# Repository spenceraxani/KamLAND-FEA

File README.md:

# KamLAND-FEA
The analog front end for MOGURA2

Datasheets:
 	This folder contains the datasheets for the desired op amps, the RF-SoC prototype board (ZCU111) and the expansion board (XM5000).

Documents:
	This contains the detailed description of the front end analog electronics reference design.

KiCAD:
	Here, the PCB design files are included for the RF-ADC and RF-DAC expansion boards.

Simulation:
	Files for the TINA-TI simulation.

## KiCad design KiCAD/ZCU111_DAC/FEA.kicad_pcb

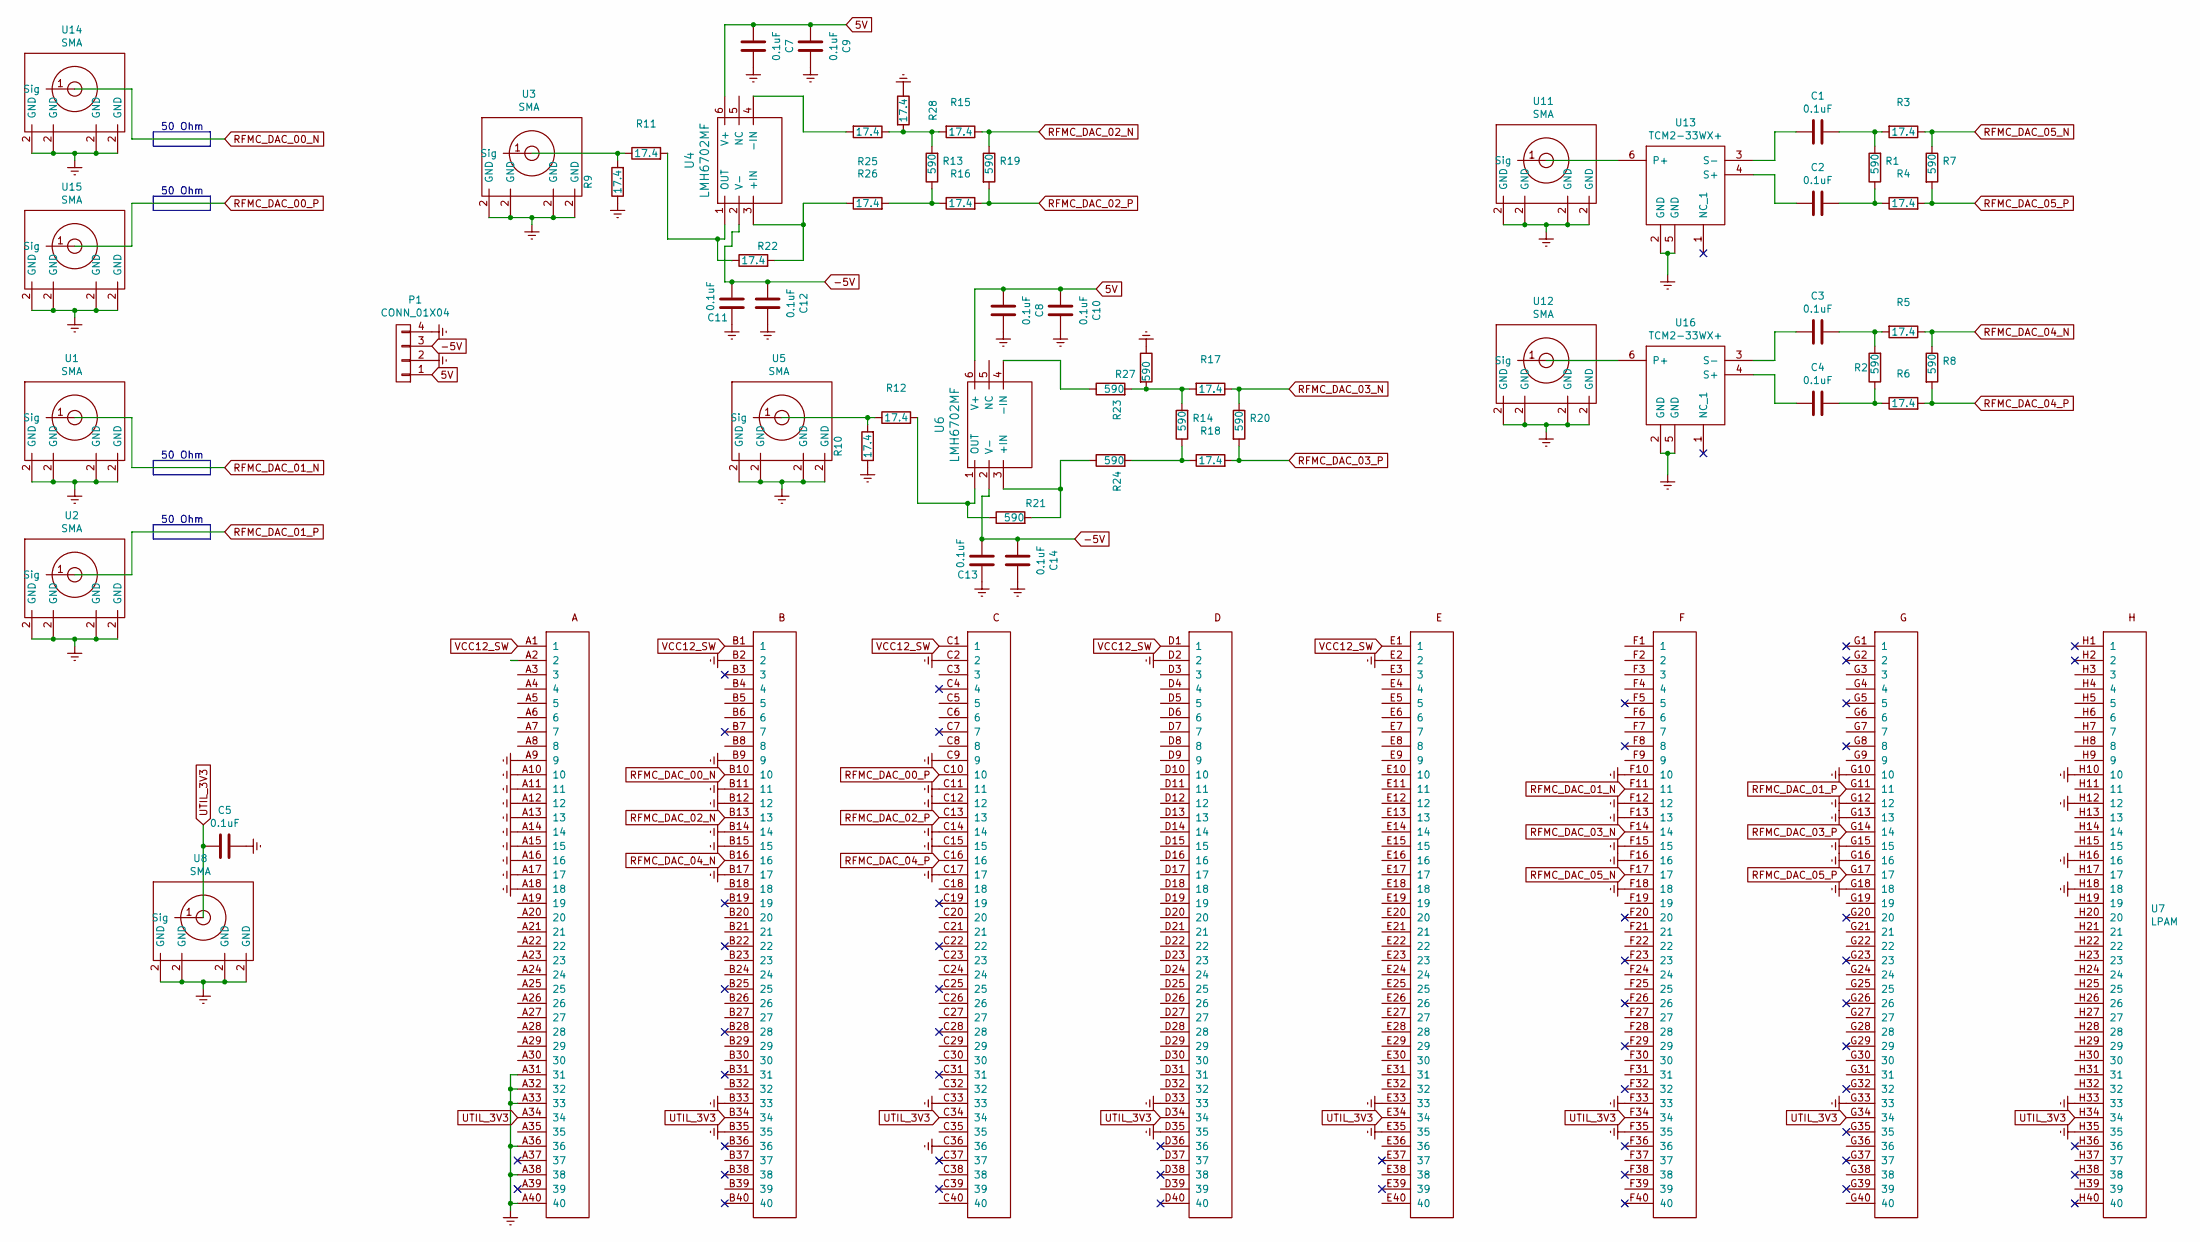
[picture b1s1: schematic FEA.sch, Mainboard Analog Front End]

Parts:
C1, C2, C3, C4, C5, C7, C8, C9, C10, C11, C12, C13, C14: 0.1uF; C_0603
P1: CONN_01X04; Pin_Header_Straight_1x04_Pitch2.54mm
R1, R2, R7, R8, R13, R14, R19, R20, R21, R23, R24, R27: 590; C_0603
R3, R4, R5, R6, R9, R10, R11, R12, R15, R16, R17, R18, R22, R25, R26, R28: 17.4; C_0603
U1, U2, U3, U5, U11, U12, U14, U15: SMA; SMA_90
U4, U6: LMH6702MF; SOT-23-6
U7: LPAM
U8: SMA; SMA_side_mount
U13, U16: TCM2-33WX+

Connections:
5V: C7.2, C8.2, C9.2, C10.2, P1.1, U4.6 (V+), U6.6 (V+)
-5V: C11.2, C12.2, C13.2, C14.2, P1.3, U4.2 (V-), U6.2 (V-)
Earth: C5.1, C7.1, C8.1, C9.1, C10.1, C11.1, C12.1, C13.1, C14.1, P1.2, P1.4, R9.1, R10.1, R27.1, R28.1, U1.2 (GND), U2.2 (GND), U3.2 (GND), U5.2 (GND), U7.A9 (9), U7.A10 (10), U7.A11 (11), U7.A12 (12), U7.A13 (13), U7.A14 (14), U7.A15 (15), U7.A16 (16), U7.A17 (17), U7.A18 (18), U7.A31 (31), U7.A32 (32), U7.A33 (33), U7.A36 (36), U7.A38 (38), U7.A40 (40), U7.B2 (2), U7.B9 (9), U7.B11 (11), U7.B12 (12), U7.B14 (14), U7.B15 (15), U7.B17 (17), U7.B33 (33), U7.B35 (35), U7.C2 (2), U7.C9 (9), U7.C11 (11), U7.C12 (12), U7.C14 (14), U7.C15 (15), U7.C17 (17), U7.C33 (33), U7.C36 (36), U7.D2 (2), U7.D33 (33), U7.D35 (35), U7.E2 (2), U7.E33 (33), U7.E35 (35), U7.F10 (10), U7.F12 (12), U7.F13 (13), U7.F15 (15), U7.F16 (16), U7.F18 (18), U7.F33 (33), U7.F35 (35), U7.G10 (10), U7.G12 (12), U7.G13 (13), U7.G15 (15), U7.G16 (16), U7.G18 (18), U7.G33 (33), U7.H10 (10), U7.H12 (12), U7.H16 (16), U7.H18 (18), U7.H33 (33), U7.H35 (35), U8.2 (GND), U11.2 (GND), U12.2 (GND), U13.2 (GND), U13.5 (GND), U14.2 (GND), U15.2 (GND), U16.2 (GND), U16.5 (GND)
unnamed: C1.1, R1.2, R3.2
unnamed: C1.2, U13.3 (S-)
unnamed: C2.1, R1.1, R4.1
unnamed: C2.2, U13.4 (S+)
unnamed: C3.1, R2.2, R5.2
unnamed: C3.2, U16.3 (S-)
unnamed: C4.1, R2.1, R6.1
unnamed: C4.2, U16.4 (S+)
unnamed: R10.2, R12.1, U5.1 (Sig)
unnamed: R9.2, R11.1, U3.1 (Sig)
unnamed: R11.2, R22.1, U4.1 (OUT)
unnamed: R12.2, R21.1, U6.1 (OUT)
unnamed: R13.1, R16.1, R26.2
unnamed: R13.2, R15.2, R25.1, R28.2
unnamed: R14.1, R18.1, R24.2
unnamed: R14.2, R17.2, R23.2, R27.2
unnamed: R21.2, R24.1, U6.3 (+IN)
unnamed: R22.2, R26.1, U4.3 (+IN)
unnamed: R23.1, U6.4 (-IN)
unnamed: R25.2, U4.4 (-IN)
unnamed: U11.1 (Sig), U13.6 (P+)
unnamed: U12.1 (Sig), U16.6 (P+)
RFMC_DAC_00_N: U7.B10 (10), U14.1 (Sig)
RFMC_DAC_00_P: U7.C10 (10), U15.1 (Sig)
RFMC_DAC_01_N: U1.1 (Sig), U7.F11 (11)
RFMC_DAC_01_P: U2.1 (Sig), U7.G11 (11)
RFMC_DAC_02_N: R15.1, R19.1, U7.B13 (13)
RFMC_DAC_02_P: R16.2, R19.2, U7.C13 (13)
RFMC_DAC_03_N: R17.1, R20.1, U7.F14 (14)
RFMC_DAC_03_P: R18.2, R20.2, U7.G14 (14)
RFMC_DAC_04_N: R5.1, R8.1, U7.B16 (16)
RFMC_DAC_04_P: R6.2, R8.2, U7.C16 (16)
RFMC_DAC_05_N: R3.1, R7.1, U7.F17 (17)
RFMC_DAC_05_P: R4.2, R7.2, U7.G17 (17)
UTIL_3V3: C5.2, U7.A34 (34), U7.B34 (34), U7.C34 (34), U7.D34 (34), U7.E34 (34), U7.F34 (34), U7.G34 (34), U7.H34 (34), U8.1 (Sig)
VCC12_SW: U7.A1 (1), U7.B1 (1), U7.C1 (1), U7.D1 (1), U7.E1 (1)

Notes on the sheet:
50 Ohm

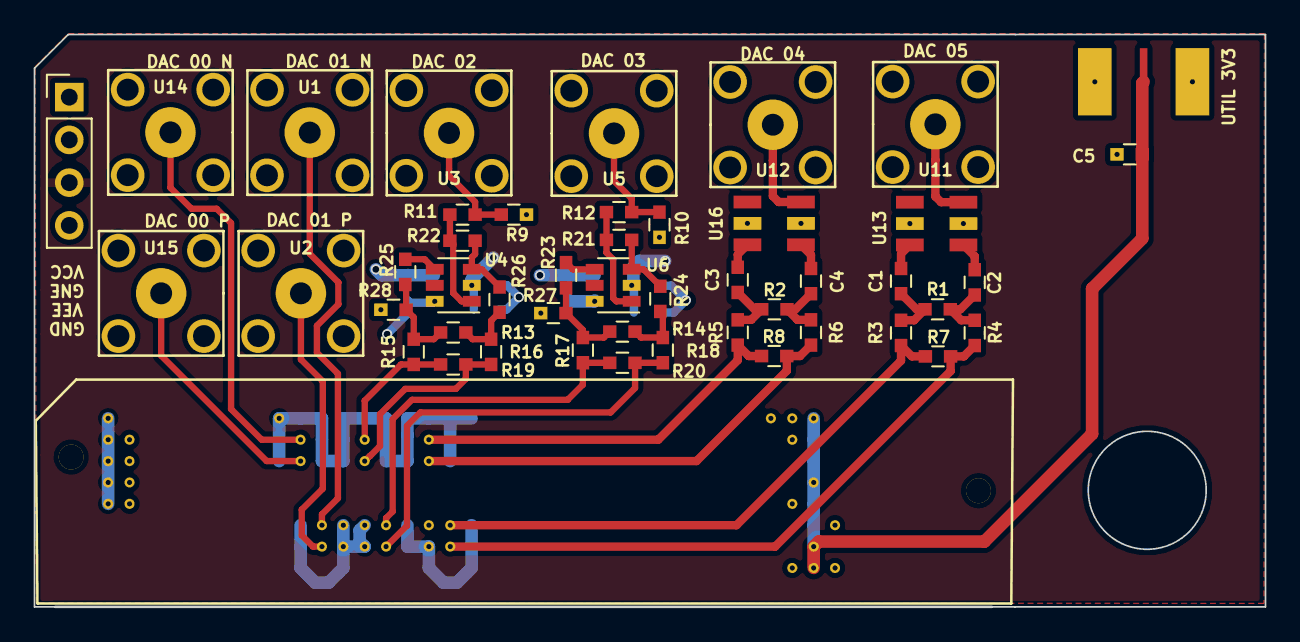
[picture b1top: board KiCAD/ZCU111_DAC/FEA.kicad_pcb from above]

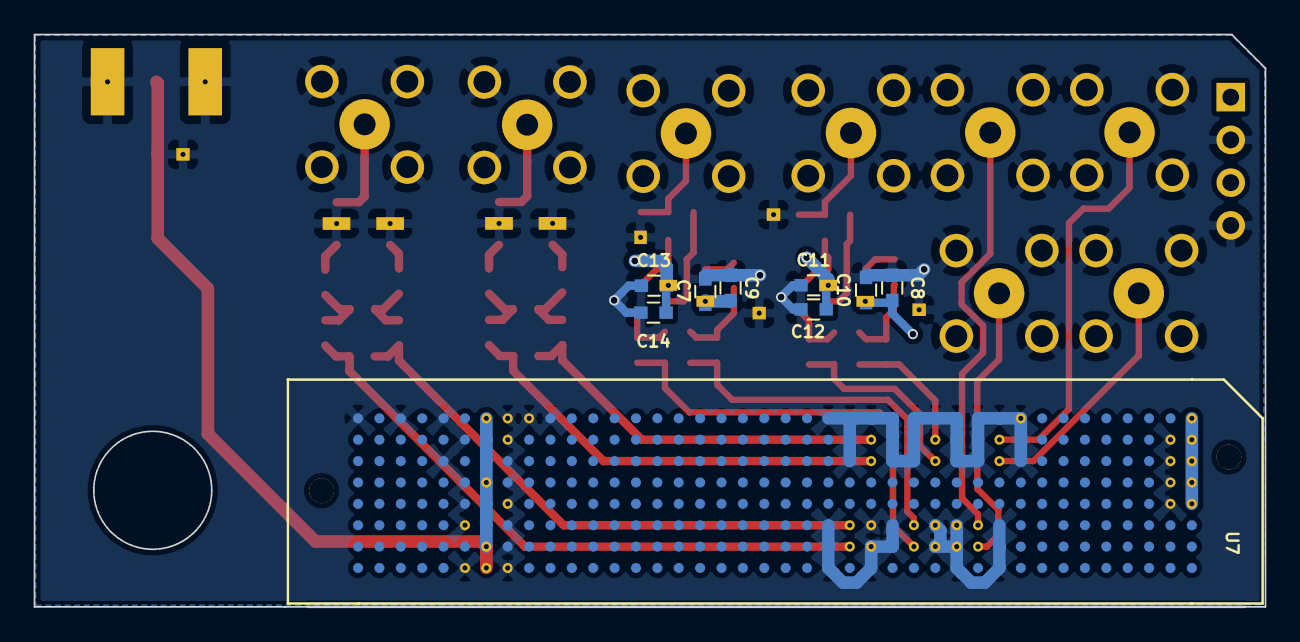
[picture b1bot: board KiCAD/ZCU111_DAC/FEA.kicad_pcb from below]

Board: 4 copper layers, 73.1 x 34.0 mm, 56 parts (9 on the bottom side), 39 nets.

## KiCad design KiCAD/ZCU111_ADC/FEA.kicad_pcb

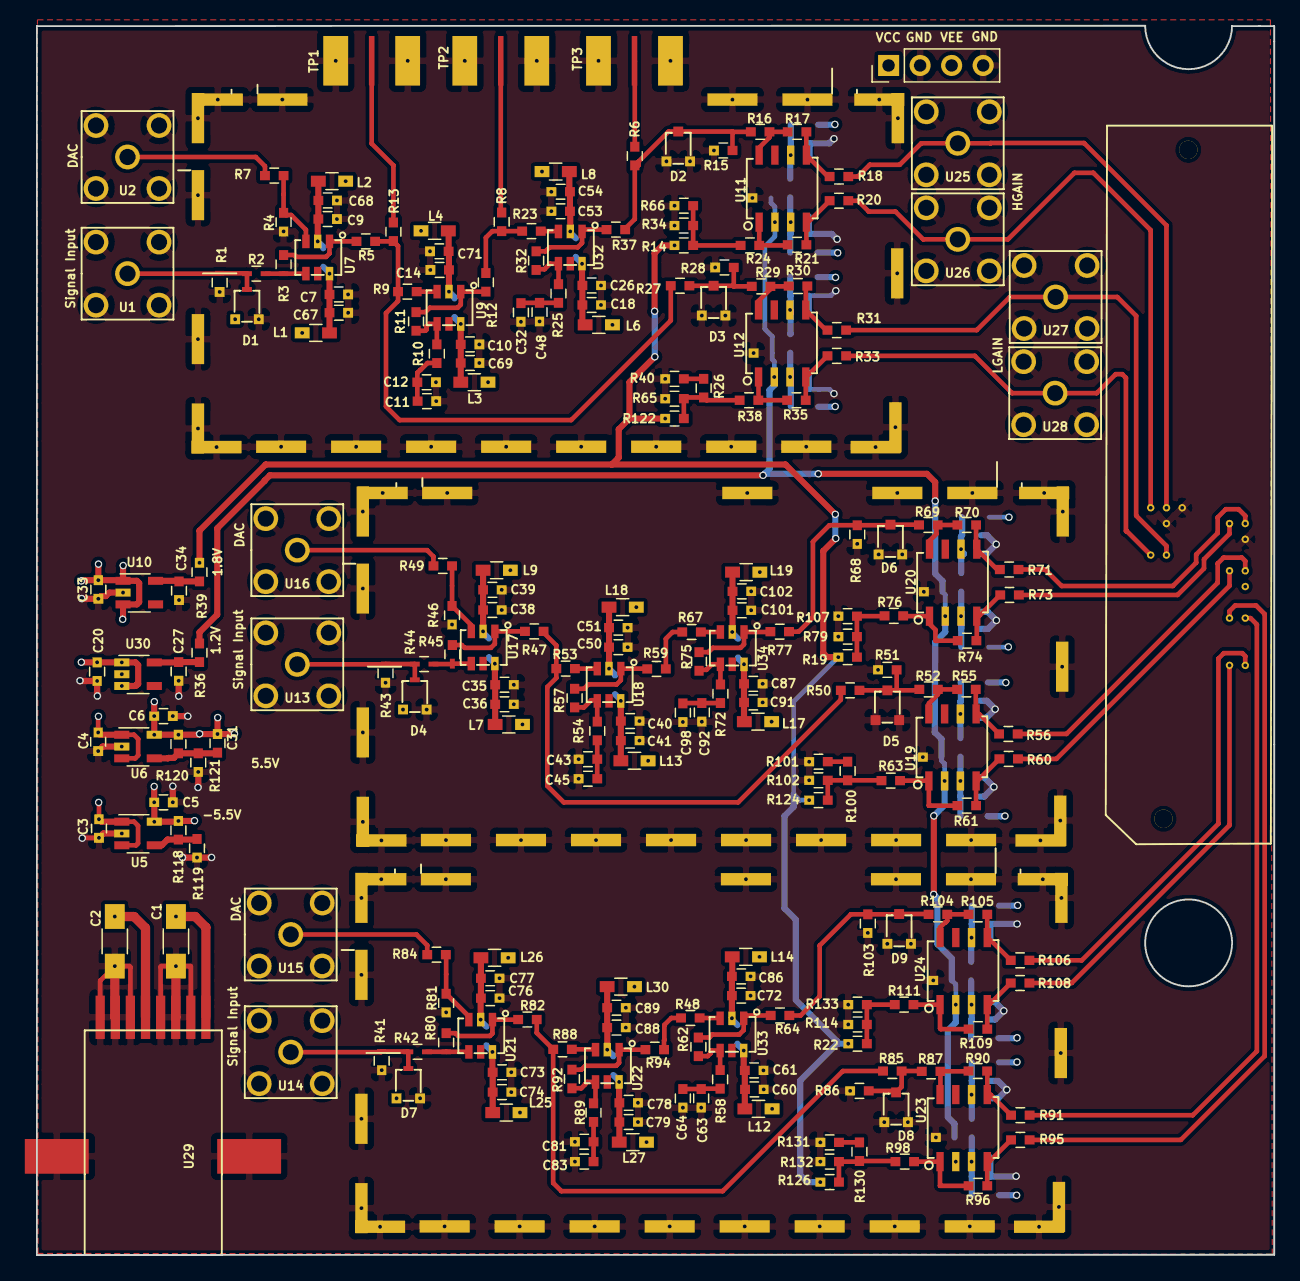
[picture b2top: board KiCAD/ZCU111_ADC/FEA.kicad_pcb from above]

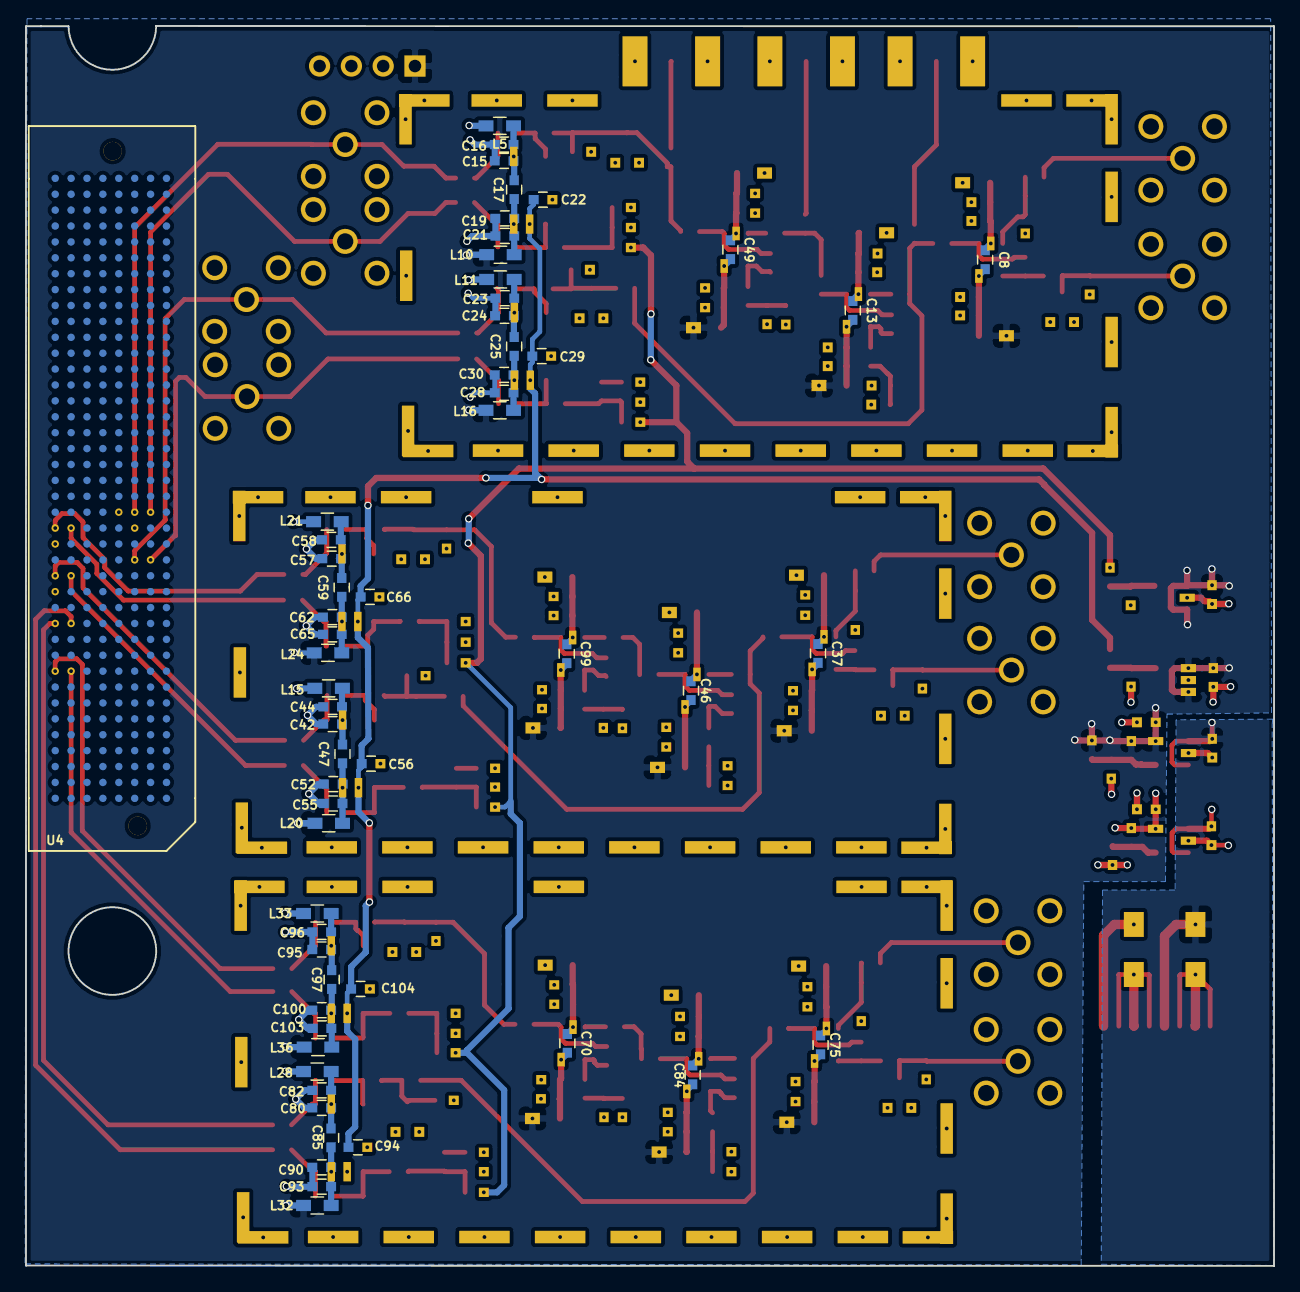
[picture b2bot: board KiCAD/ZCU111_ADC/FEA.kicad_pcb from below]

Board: 4 copper layers, 99.7 x 99.1 mm, 298 parts (58 on the bottom side), 142 nets.

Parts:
C1, C2: CP1; C_1206_HandSoldering
C3, C5, C6: 2.2uF; C_0603
C4, C20, C33: 1uF; C_0603
C7, C8, C9, C10, C11, C13, C14, C16, C19, C24, C26, C30, C32, C36, C37, C38, C41, C43, C44, C46, C49, C50, C52, C53, C58, C61, C62, C63, C70, C72, C74, C75, C76, C79, C81, C82, C84, C88, C90, C91, C92, C96, C99, C100, C101: 10nF; C_0603
C12, C45, C48, C64, C83, C98: 100nF; C_0603
C15, C18, C21, C22, C23, C28, C29, C35, C40, C42, C51, C54, C55, C56, C57, C60, C65, C66, C67, C69, C71, C73, C78, C80, C86, C87, C89, C93, C94, C95, C102, C103, C104: 0.1uF; C_0603
C17, C25, C47, C59, C85, C97: 0.01uF; C_0603
C27, C34: 10uF; C_0603
C31: 470pF; C_0603
C39, C68, C77: 0.1nF; C_0603
D1, D2, D3, D4, D5, D6, D7, D8, D9: RB706D
L1, L2, L3, L4, L5, L6, L7, L8, L9, L10, L11, L12, L13, L14, L15, L16, L17, L18, L19, L20, L21, L24, L25, L26, L27, L28, L30, L32, L33, L36: BLM18BB221SN1; R_0603_HandSoldering
P1: CONN_01X04; Pin_Header_Straight_1x04_Pitch2.54mm
P2, P3, P4: CONN_01X01; RF SHIELD 1.094 X 2.23 SMD
R1, R41, R43: 54.9; C_0603
R2, R3, R42, R44, R45, R80: 560; C_0603
R4, R46, R81: 25.5; C_0603
R5, R9, R12, R18, R20, R23, R26, R28, R31, R33, R37, R47, R48, R51, R53, R56, R59, R60, R64, R65, R66, R67, R71, R73, R77, R82, R86, R88, R91, R94, R95, R100, R102, R106, R107, R108, R130, R132, R133: 49.9; C_0603
R6, R8, R13: R; C_0603
R7, R49, R84: 10k; C_0603
R10, R25, R54, R58, R72, R89: 100; C_0603
R11, R32, R57, R62, R75, R92: 390; C_0603
R14, R19, R22, R27, R40, R50, R85, R101, R122, R124, R126, R131: 200; C_0603
R15, R34, R68, R79, R103, R114: 68.1; C_0603
R16, R24, R69, R76, R104, R111: 127; C_0603
R17, R21, R30, R35, R55, R61, R70, R74, R90, R96, R105, R109: 274; C_0603
R29, R38, R52, R63, R87, R98: 255; C_0603
R36, R39: 0; C_0603
R118: 21k; C_0603
R119, R121: 75k; C_0603
R120: 22.1k; C_0603
U1, U2, U13, U14, U15, U16, U25, U26, U27, U28: SMA; SMA_90
U3, U8, U31: SMA; SMA_side_mount
U4: LPAM
U5, U6, U10, U30: 5-Lead_TSOT; TSOT-23-5
U7, U9, U17, U18, U21, U22, U32, U33, U34: LMH6702MF; LMH6702
U11, U12, U19, U20, U23, U24: LMH6550
U29: Ethernet

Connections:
1.2V: C22.1, C29.1, C56.1, C66.1, C94.1, C104.1, R36.1, U4.A21, U11.2, U12.2, U19.2, U20.2, U23.2, U24.2
1.8V: R14.2, R19.2, R22.2, R39.1, R122.2, R124.2, R126.2
5V: C6.1, C20.1, C31.2, C33.1, L1.2, L3.2, L6.2, L7.2, L10.1, L12.2, L13.2, L16.1, L17.2, L20.1, L24.1, L25.2, L27.2, L32.1, L36.1, P1.1, R120.2, U6.5, U10.1, U10.3, U30.1, U30.3
-5V: C5.1, D1.2, D4.2, D7.2, L2.1, L4.1, L5.2, L8.1, L9.1, L11.2, L14.1, L15.2, L18.1, L19.1, L21.2, L26.1, L28.2, L30.1, L33.2, P1.3, R118.1, U5.5
/Amp1/DAC_input: R7.1, U2.1
/Amp1/Sig_in: D1.3, R1.1, R2.2, U1.1
/Amp1/TP1: R5.1, R9.2, R13.1, R27.2
/Amp1/TP2: R8.1, R12.1, R23.2
/Amp1/TP3: D2.3, R6.1, R15.1, R16.2, R37.1
/sheet5EE0D7D6/DAC_input: R49.1, U16.1
/sheet5EE0D7D6/Sig_in: D4.3, R43.1, R44.2, U13.1
/sheet5EE0D7D6/TP1: R47.1, R50.2, R53.2
/sheet5EE0D7D6/TP2: R59.1, R67.2
/sheet5EE0D7D6/TP3: D6.3, R68.1, R69.2, R77.1
/sheet5F00471B/DAC_input: R84.1, U15.1
/sheet5F00471B/Sig_in: D7.3, R41.1, R42.2, U14.1
/sheet5F00471B/TP1: R82.1, R85.2, R88.2
/sheet5F00471B/TP2: R48.2, R94.1
/sheet5F00471B/TP3: D9.3, R64.1, R103.1, R104.2
Earth: C1.2, C2.1, C3.2, C4.2, C5.2, C6.2, C7.1, C9.1, C10.1, C11.1, C12.1, C14.1, C15.1, C16.1, C18.1, C19.1, C20.2, C21.1, C22.2, C23.1, C24.1, C26.1, C27.2, C28.1, C29.2, C30.1, C32.1, C33.2, C34.2, C35.1, C36.1, C38.1, C39.1, C40.1, C41.1, C42.1, C43.1, C44.1, C45.1, C48.1, C50.1, C51.1, C52.1, C53.1, C54.1, C55.1, C56.2, C57.1, C58.1, C60.1, C61.1, C62.1, C63.1, C64.1, C65.1, C66.2, C67.1, C68.1, C69.1, C71.1, C72.1, C73.1, C74.1, C76.1, C77.1, C78.1, C79.1, C80.1, C81.1, C82.1, C83.1, C86.1, C87.1, C88.1, C89.1, C90.1, C91.1, C92.1, C93.1, C94.2, C95.1, C96.1, C98.1, C100.1, C101.1, C102.1, C103.1, C104.2, D1.1, D2.1, D2.2, D3.1, D3.2, D4.1, D5.1, D5.2, D6.1, D6.2, D7.1, D8.1, D8.2, D9.1, D9.2, P1.2, P1.4, P2.1, P3.1, P4.1, R1.2, R4.1, R15.2, R28.2, R34.1, R40.1, R41.2, R43.2, R46.1, R51.2, R65.1, R66.1, R68.2, R79.1, R81.1, R86.2, R101.1, R102.1, R103.2, R107.1, R114.1, R119.1, R121.1, R131.1, R132.1, R133.1, U1.2, U2.2, U3.2, U4.A5, U4.A8, U4.B15, U4.C15, U4.C18, U4.D19, U4.H17, U5.2, U6.2, U8.2, U10.2, U13.2, U14.2, U15.2, U16.2, U25.2, U26.2, U27.2, U28.2, U29.0, U29.1, U29.2, U29.3, U29.5, U29.6, U29.7, U30.2, U31.2
unnamed: C1.1, C3.1, U5.1, U5.3, U29.8
unnamed: C2.2, C4.1, U6.1, U6.3, U29.4
unnamed: C10.2, C13.2, C69.2, L3.1, U9.6
unnamed: C11.2, C12.2, R10.1
unnamed: C13.1, C14.2, C71.2, L4.2, U9.2
unnamed: C15.2, C16.2, C17.2, L5.1, U11.6
unnamed: C17.1, C19.2, C21.2, L10.2, U11.3
unnamed: C18.2, C26.2, C49.2, L6.1, U32.6
unnamed: C23.2, C24.2, C25.2, L11.1, U12.6
unnamed: C25.1, C28.2, C30.2, L16.2, U12.3
unnamed: C27.1, R36.2, U30.5
unnamed: C31.1, R120.1, R121.2, U6.4
unnamed: C32.2, C48.2, R25.1
unnamed: C34.1, R39.2, U10.5
unnamed: C35.2, C36.2, C37.2, L7.1, U17.6
unnamed: C37.1, C38.2, C39.2, L9.2, U17.2
unnamed: C40.2, C41.2, C46.2, L13.1, U18.6
unnamed: C42.2, C44.2, C47.2, L15.1, U19.6
unnamed: C43.2, C45.2, R54.1
unnamed: C46.1, C50.2, C51.2, L18.2, U18.2
unnamed: C47.1, C52.2, C55.2, L20.2, U19.3
unnamed: C49.1, C53.2, C54.2, L8.2, U32.2
unnamed: C57.2, C58.2, C59.2, L21.1, U20.6
unnamed: C59.1, C62.2, C65.2, L24.2, U20.3
unnamed: C60.2, C61.2, C70.2, L12.1, U33.6
unnamed: C63.2, C64.2, R58.1
unnamed: C7.2, C8.2, C67.2, L1.1, U7.6
unnamed: C8.1, C9.2, C68.2, L2.2, U7.2
unnamed: C70.1, C72.2, C86.2, L14.2, U33.2
unnamed: C73.2, C74.2, C75.2, L25.1, U21.6
unnamed: C75.1, C76.2, C77.2, L26.2, U21.2
unnamed: C78.2, C79.2, C84.2, L27.1, U22.6
unnamed: C80.2, C82.2, C85.2, L28.1, U23.6
unnamed: C81.2, C83.2, R89.1
unnamed: C84.1, C88.2, C89.2, L30.2, U22.2
unnamed: C85.1, C90.2, C93.2, L32.2, U23.3
unnamed: C87.2, C91.2, C99.2, L17.1, U34.6
unnamed: C92.2, C98.2, R72.1
unnamed: C95.2, C96.2, C97.2, L33.1, U24.6
unnamed: C97.1, C100.2, C103.2, L36.2, U24.3
unnamed: C99.1, C101.2, C102.2, L19.2, U34.2
unnamed: D3.3, R27.1, R28.1, R29.2
unnamed: D5.3, R50.1, R51.1, R52.2
unnamed: D8.3, R85.1, R86.1, R87.2
unnamed: R2.1, R3.2, U7.4
unnamed: R3.1, R5.2, U7.1
unnamed: R4.2, R7.2, U7.3
unnamed: R6.2, U31.1
unnamed: R8.2, U3.1
unnamed: R9.1, U9.3
unnamed: R10.2, R11.2, U9.4
unnamed: R11.1, R12.2, U9.1
unnamed: R13.2, U8.1
unnamed: R14.1, R24.2, R34.2, R66.2
unnamed: R16.1, R17.2, U11.8
unnamed: R17.1, R18.2, U11.5
unnamed: R20.2, R21.2, U11.4
unnamed: R21.1, R24.1, U11.1
unnamed: R23.1, U32.3
unnamed: R25.2, R32.2, U32.4
unnamed: R26.1, R40.2
unnamed: R29.1, R30.2, U12.8
unnamed: R30.1, R31.2, U12.5
unnamed: R32.1, R37.2, U32.1
unnamed: R33.2, R35.2, U12.4
unnamed: R35.1, R38.1, U12.1
unnamed: R42.1, R80.2, U21.4
unnamed: R44.1, R45.2, U17.4
unnamed: R45.1, R47.2, U17.1
unnamed: R46.2, R49.2, U17.3
unnamed: R48.1, U33.3
unnamed: R52.1, R55.2, U19.8
unnamed: R53.1, U18.3
unnamed: R54.2, R57.2, U18.4
unnamed: R55.1, R56.2, U19.5
unnamed: R57.1, R59.2, U18.1
unnamed: R58.2, R62.2, U33.4
unnamed: R60.2, R61.2, U19.4
unnamed: R61.1, R63.1, U19.1
unnamed: R62.1, R64.2, U33.1
unnamed: R67.1, U34.3
unnamed: R69.1, R70.2, U20.8
unnamed: R70.1, R71.2, U20.5
unnamed: R72.2, R75.2, U34.4
unnamed: R73.2, R74.2, U20.4
unnamed: R74.1, R76.1, U20.1
unnamed: R75.1, R77.2, U34.1
unnamed: R80.1, R82.2, U21.1
unnamed: R81.2, R84.2, U21.3
unnamed: R87.1, R90.2, U23.8
unnamed: R88.1, U22.3
unnamed: R89.2, R92.2, U22.4
unnamed: R90.1, R91.2, U23.5
unnamed: R92.1, R94.2, U22.1
unnamed: R95.2, R96.2, U23.4
unnamed: R96.1, R98.1, U23.1
unnamed: R100.1, R101.2
unnamed: R63.2, R100.2, R102.2, R124.1
unnamed: R104.1, R105.2, U24.8
unnamed: R105.1, R106.2, U24.5
unnamed: R19.1, R76.2, R79.2, R107.2
unnamed: R108.2, R109.2, U24.4
unnamed: R109.1, R111.1, U24.1
unnamed: R22.1, R111.2, R114.2, R133.2
unnamed: R118.2, R119.2, U5.4
unnamed: R26.2, R38.2, R65.2, R122.1
unnamed: R98.2, R126.1, R130.2, R132.2
unnamed: R130.1, R131.2
RFMC_ADC_00_N: R108.1, U4.G9
RFMC_ADC_00_P: R106.1, U4.H9
RFMC_ADC_02_N: R95.1, U4.G12
RFMC_ADC_02_P: R91.1, U4.H12
RFMC_ADC_04_N: R60.1, U4.G15
RFMC_ADC_04_P: R56.1, U4.H15
RFMC_ADC_05_N: R33.1, U4.B16, U28.1
RFMC_ADC_05_P: R31.1, U4.C16, U27.1
RFMC_ADC_06_N: R73.1, U4.G18
RFMC_ADC_06_P: R71.1, U4.H18
RFMC_ADC_07_N: R20.1, U4.B19, U26.1
RFMC_ADC_07_P: R18.1, U4.C19, U25.1
UTIL_3V3: U4.A7, U4.B7, U4.C7, U4.D7, U4.E7, U4.F7, U4.G7, U4.H7
VCC1V8_Bus: U4.A6, U4.C6
